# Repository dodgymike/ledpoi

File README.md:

# ledpoi
LED Poi

Hardware design and software for an LED-based fire-poi

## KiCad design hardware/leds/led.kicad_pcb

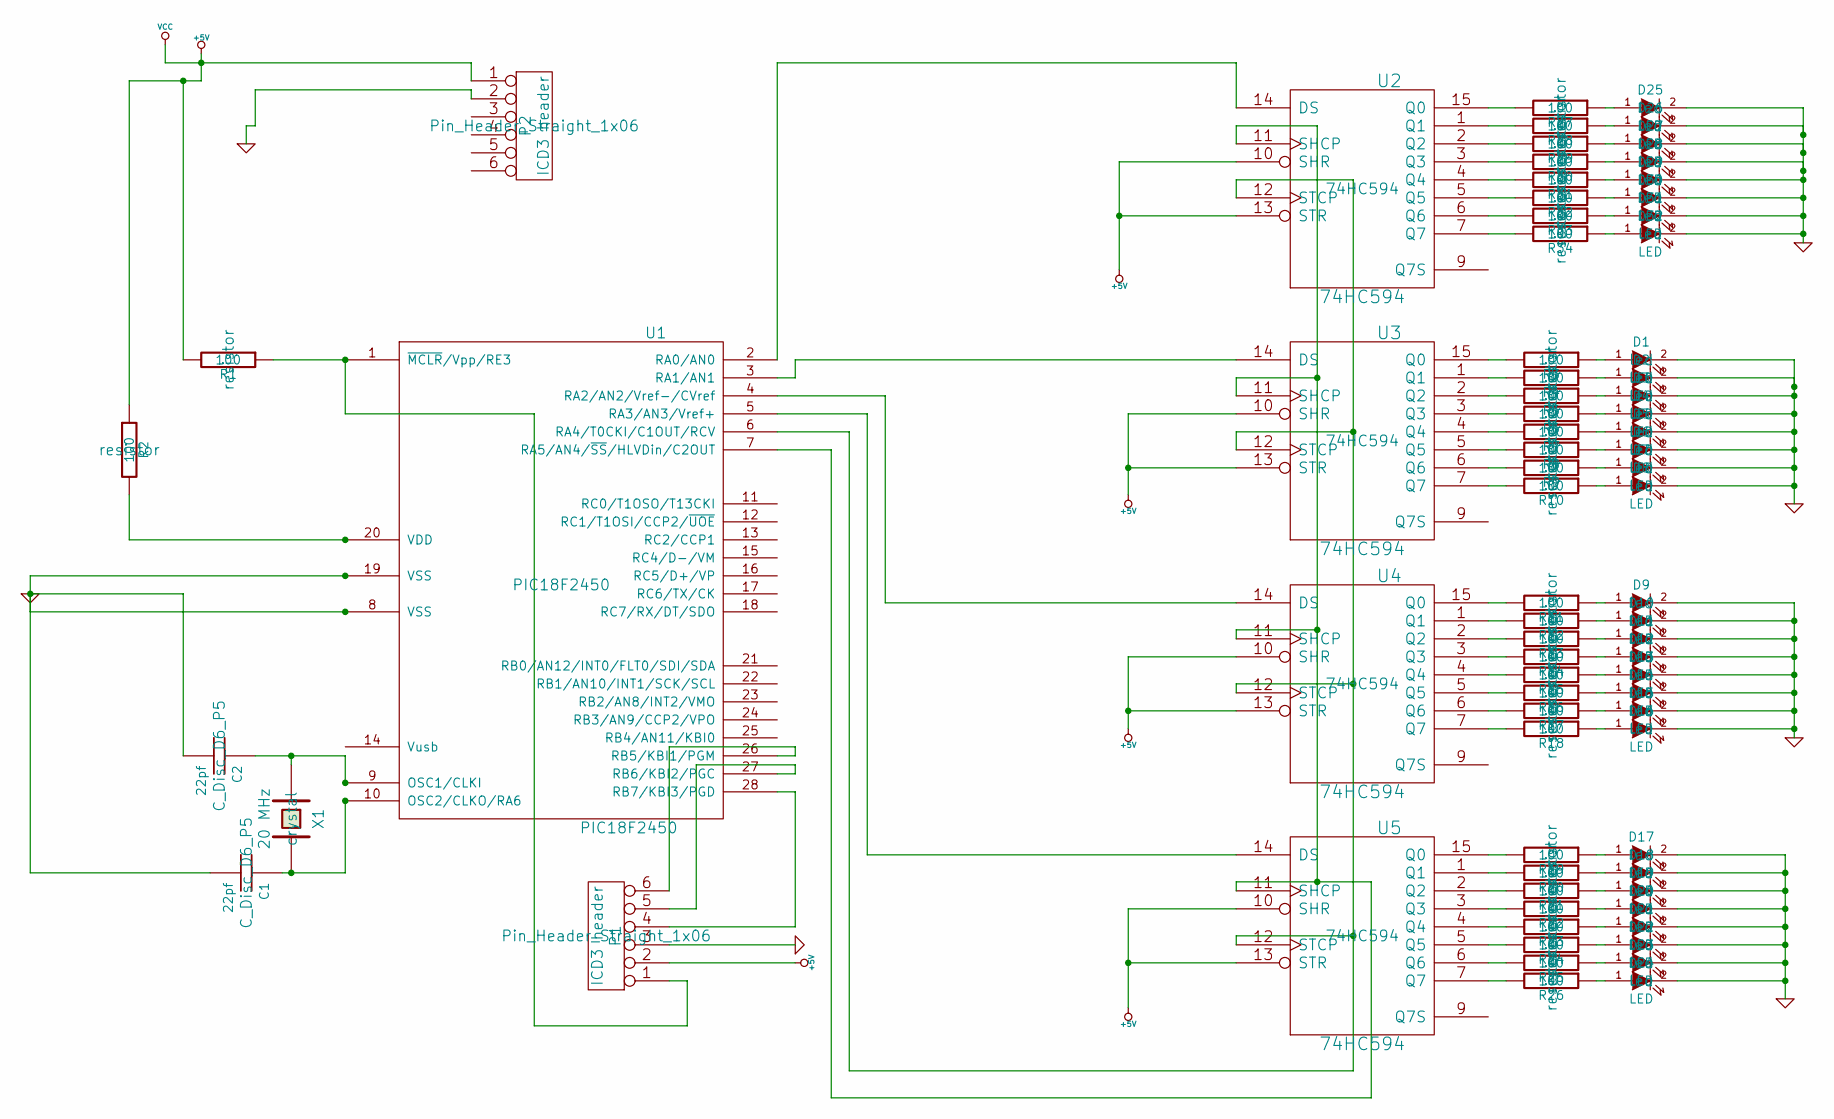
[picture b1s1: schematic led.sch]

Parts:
C1, C2: 22pf; C_Disc_D6_P5
D1, D2, D3, D4, D5, D6, D7, D8, D9, D10, D11, D12, D13, D14, D15, D16, D17, D18, D19, D20, D21, D22, D23, D24, D25, D26, D27, D28, D29, D30, D31, D32: LED; led
P1, P2: ICD3 header; Pin_Header_Straight_1x06
R1, R2, R3, R4, R5, R6, R7, R8, R9, R10, R11, R12, R13, R14, R15, R16, R17, R18, R19, R20, R21, R22, R23, R24, R25, R26, R27, R28, R29, R30, R31, R32, R33, R34: 100; resistor
U1: PIC18F2450
U2, U3, U4, U5: 74HC594
X1: 20 MHz; crystal

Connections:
+5V: P1.2, P2.1, R1.2, R2.1, U2.10 (SHR), U2.13 (STR), U2.16 (VCC), U3.10 (SHR), U3.13 (STR), U3.16 (VCC), U4.10 (SHR), U4.13 (STR), U4.16 (VCC), U5.10 (SHR), U5.13 (STR), U5.16 (VCC)
GND: C1.2, C2.2, D1.2 (K), D2.2 (K), D3.2 (K), D4.2 (K), D5.2 (K), D6.2 (K), D7.2 (K), D8.2 (K), D9.2 (K), D10.2 (K), D11.2 (K), D12.2 (K), D13.2 (K), D14.2 (K), D15.2 (K), D16.2 (K), D17.2 (K), D18.2 (K), D19.2 (K), D20.2 (K), D21.2 (K), D22.2 (K), D23.2 (K), D24.2 (K), D25.2 (K), D26.2 (K), D27.2 (K), D28.2 (K), D29.2 (K), D30.2 (K), D31.2 (K), D32.2 (K), P1.3, P2.2, U1.8 (VSS), U1.19 (VSS), U2.8 (GND), U3.8 (GND), U4.8 (GND), U5.8 (GND)
unnamed: C1.1, U1.10 (OSC2/CLKO/RA6), X1.2
unnamed: C2.1, U1.9 (OSC1/CLKI), X1.1
unnamed: D1.1 (A), R3.1
unnamed: D2.1 (A), R4.1
unnamed: D3.1 (A), R5.1
unnamed: D4.1 (A), R6.1
unnamed: D5.1 (A), R7.1
unnamed: D6.1 (A), R8.1
unnamed: D7.1 (A), R9.1
unnamed: D8.1 (A), R10.1
unnamed: D9.1 (A), R11.1
unnamed: D10.1 (A), R12.1
unnamed: D11.1 (A), R13.1
unnamed: D12.1 (A), R14.1
unnamed: D13.1 (A), R15.1
unnamed: D14.1 (A), R16.1
unnamed: D15.1 (A), R17.1
unnamed: D16.1 (A), R18.1
unnamed: D17.1 (A), R19.1
unnamed: D18.1 (A), R20.1
unnamed: D19.1 (A), R21.1
unnamed: D20.1 (A), R22.1
unnamed: D21.1 (A), R23.1
unnamed: D22.1 (A), R24.1
unnamed: D23.1 (A), R25.1
unnamed: D24.1 (A), R26.1
unnamed: D25.1 (A), R27.1
unnamed: D26.1 (A), R28.1
unnamed: D27.1 (A), R29.1
unnamed: D28.1 (A), R30.1
unnamed: D29.1 (A), R31.1
unnamed: D30.1 (A), R32.1
unnamed: D31.1 (A), R33.1
unnamed: D32.1 (A), R34.1
unnamed: P1.1, R1.1, U1.1 (~MCLR~/Vpp/RE3)
unnamed: P1.4, U1.28 (RB7/KBI3/PGD)
unnamed: P1.5, U1.27 (RB6/KBI2/PGC)
unnamed: P1.6, U1.26 (RB5/KBI1/PGM)
unnamed: R2.2, U1.20 (VDD)
unnamed: R3.2, U3.15 (Q0)
unnamed: R4.2, U3.1 (Q1)
unnamed: R5.2, U3.2 (Q2)
unnamed: R6.2, U3.3 (Q3)
unnamed: R7.2, U3.4 (Q4)
unnamed: R8.2, U3.5 (Q5)
unnamed: R9.2, U3.6 (Q6)
unnamed: R10.2, U3.7 (Q7)
unnamed: R11.2, U4.15 (Q0)
unnamed: R12.2, U4.1 (Q1)
unnamed: R13.2, U4.2 (Q2)
unnamed: R14.2, U4.3 (Q3)
unnamed: R15.2, U4.4 (Q4)
unnamed: R16.2, U4.5 (Q5)
unnamed: R17.2, U4.6 (Q6)
unnamed: R18.2, U4.7 (Q7)
unnamed: R19.2, U5.15 (Q0)
unnamed: R20.2, U5.1 (Q1)
unnamed: R21.2, U5.2 (Q2)
unnamed: R22.2, U5.3 (Q3)
unnamed: R23.2, U5.4 (Q4)
unnamed: R24.2, U5.5 (Q5)
unnamed: R25.2, U5.6 (Q6)
unnamed: R26.2, U5.7 (Q7)
unnamed: R27.2, U2.15 (Q0)
unnamed: R28.2, U2.1 (Q1)
unnamed: R29.2, U2.2 (Q2)
unnamed: R30.2, U2.3 (Q3)
unnamed: R31.2, U2.4 (Q4)
unnamed: R32.2, U2.5 (Q5)
unnamed: R33.2, U2.6 (Q6)
unnamed: R34.2, U2.7 (Q7)
unnamed: U1.2 (RA0/AN0), U2.14 (DS)
unnamed: U1.3 (RA1/AN1), U3.14 (DS)
unnamed: U1.4 (RA2/AN2/Vref-/CVref), U4.14 (DS)
unnamed: U1.5 (RA3/AN3/Vref+), U5.14 (DS)
unnamed: U1.6 (RA4/T0CKI/C1OUT/RCV), U2.12 (STCP), U3.12 (STCP), U4.12 (STCP), U5.12 (STCP)
unnamed: U1.7 (RA5/AN4/~SS~/HLVDin/C2OUT), U2.11 (SHCP), U3.11 (SHCP), U4.11 (SHCP), U5.11 (SHCP)

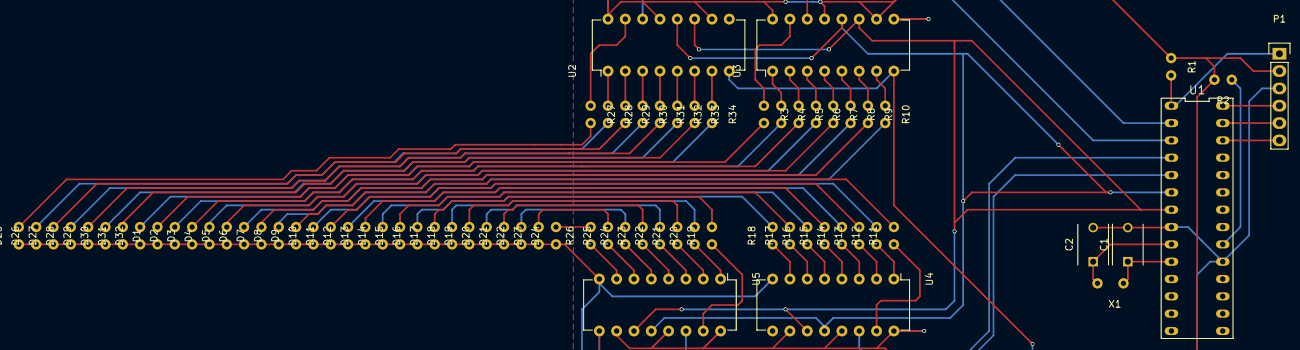
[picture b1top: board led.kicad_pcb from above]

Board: 2 copper layers, 75 parts (0 on the bottom side), 79 nets.

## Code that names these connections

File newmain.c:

/*
 * File:   newmain.c
 * Author: mike
 *
 * Created on 14 January 2016, 11:07 PM
 */

#include <pic18f2455.h>
//#include <delays.h>
#include "config.h"

//unsigned long patterns[] = {
//    0b1111111111111111,
//    0b1111111001111111,
//    0b1111110000111111,
//    0b1111100000011111,
//    0b1111000000001111,
//    0b1110000000000111,
//    0b1100000000000011,
//    0b1110000000000111,
//    0b1111000000001111,
//    0b1111100000011111,
//    0b1111110000111111,
//    0b1111111001111111
//};
unsigned long patterns[4][12] = {
    {
    0b1111111111111111,
    0b1111111111111111,
    0b1111111111111111,
    0b1111111111111111,
    0b1100000000000011,
    0b1100000000000011,
    0b1100000000000011,
    0b1100000000000011,
    0b1100000000000011,
    0b1100000000000011,
    0b1100000000000011,
    0b1111111111111111
    },
    {
    0b1111111111111111,
    0b1111111011111111,
    0b1111111011111111,
    0b1111110001111111,
    0b1111000000011111,
    0b1000000000000011,
    0b1111000000011111,
    0b1111110001111111,
    0b1111111011111111,
    0b1111111011111111,
    0b1111111111111111,
    0b1111111111111111,
    },
    {
    0b1111111111111111,
    0b1111111111111111,
    0b1111111110001111,
    0b1111110000000011,
    0b1111000000000001,
    0b1100000000000111,
    0b1000000000001111,
    0b1100000000000111,
    0b1111000000000001,
    0b1111110000000011,
    0b1111111110001111,
    0b1111111111111111
    },
    {
    0b1111111111111111,
    0b1111111001111111,
    0b1111110000111111,
    0b1111100000011111,
    0b1111000000001111,
    0b1110000000000111,
    0b1100000000000011,
    0b1110000000000111,
    0b1111000000001111,
    0b1111100000011111,
    0b1111110000111111,
    0b1111111001111111
    }
};

unsigned long update_leds(unsigned long pattern_group_index, unsigned long pattern_index) {
//    if(leds <= 0b0000000000000011) {
//        leds = 0b0000000000000110;
//        *direction = 1;
//    } else if(leds >= 0b1100000000000000) {
//        *direction = 0;
//        leds = 0b0110000000000000;
//    }
//    
//    if(*direction == 0) {
//        leds = (leds >> 1);
//    } else {
//        leds = (leds << 1);
//    }
//   
//    return leds;
    
    return patterns[pattern_group_index][pattern_index];
}

void delay(int delay) {
    for(int i = 0; i < delay; i++) {
        
    }
}

void main(void) {
    TRISA=0;
    TRISB=0;
    TRISC=0;
    PORTA=0xff;
    PORTB=0xff;
    PORTC=0xff;
    
    ADCON1=0b00001111;
    T1CONbits.TMR1CS = 0;
    T1CONbits.T1OSCEN = 0;
    
//    PORTE=0xff;
        
   
//    PORTAbits.RA0 = 1;
//    PORTAbits.RA1 = 0;
//    PORTAbits.RA2 = 1;
//    PORTAbits.RA3 = 0;
//    PORTAbits.RA4 = 1;
//    PORTAbits.RA5 = 0;
//    PORTAbits.RA6 = 1;
//    PORTAbits.RA7 = 03;
    
//    PORTB=0;
//    PORTA=0;
////    update_leds();
//    
//    PORTB=0xf;
    
    unsigned int direction = 1;
    unsigned long leds = 0b0000000000000011;

    unsigned long pattern_index = 0;
    unsigned long pattern_group_index = 0;
    
    while(1) {
        leds = update_leds(pattern_group_index, pattern_index++);
        if(pattern_index >=12) {
            pattern_index = 0;
            pattern_group_index++;
        }
        if(pattern_group_index >= 4) {
            pattern_group_index = 0;
        }
        
        unsigned char portb = (leds >> 8) & 0xff;
        unsigned char porta = leds & 0xff;
        unsigned char portc = (porta & 0b11100000) >> 5;
        
        PORTA = porta;
        PORTB = portb;
        PORTC = portc;
        
        delay(500);
    }
 
    return;
}

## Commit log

2016-01-15 leds flashing
2016-01-15 knight-rider
2016-01-16 working patterns
2016-01-21 moved mplab project to its own directory
2016-01-22 working with shift registers
2016-01-23 four shifters and higher res characters
2016-02-14 board design
2016-02-14 leds on the edge. routing not quite done yet
2016-02-22 not sure
2016-02-22 More compact design
2016-03-30 Kinda works with ring
2016-03-30 pushing the timing as hard as I can
2016-03-30 pulsing colours
2016-03-31 three groups of LEDs pulsing at different rates. Blue seems stuck :/
2016-03-31 spinning the LEDs around the disk
2016-04-01 512 bit colour working. timing is off for strips, works for ring
2016-04-02 Working for Chinese shop 5m 3-LED/controller strips
2016-04-02 Removed build/dist dirs from ledstrings.X + added gitignore to ignore those directories
2016-04-02 Heartspin, heartbeat both working
2016-04-04 Removed nbproject files + added them to .gitignore
2016-04-04 five strings working in a horrible way
2016-04-14 Working with 8 strings. Weird power issues causing strings to fade to red
